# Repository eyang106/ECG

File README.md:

# ECG
Extension project for E96A: Electrocardiogram engineering design class.

Contents:
- Board and schematic files for electrocardiogram PCB

Note: To view the schematic/board, you must download the repo and open the files with EAGLE

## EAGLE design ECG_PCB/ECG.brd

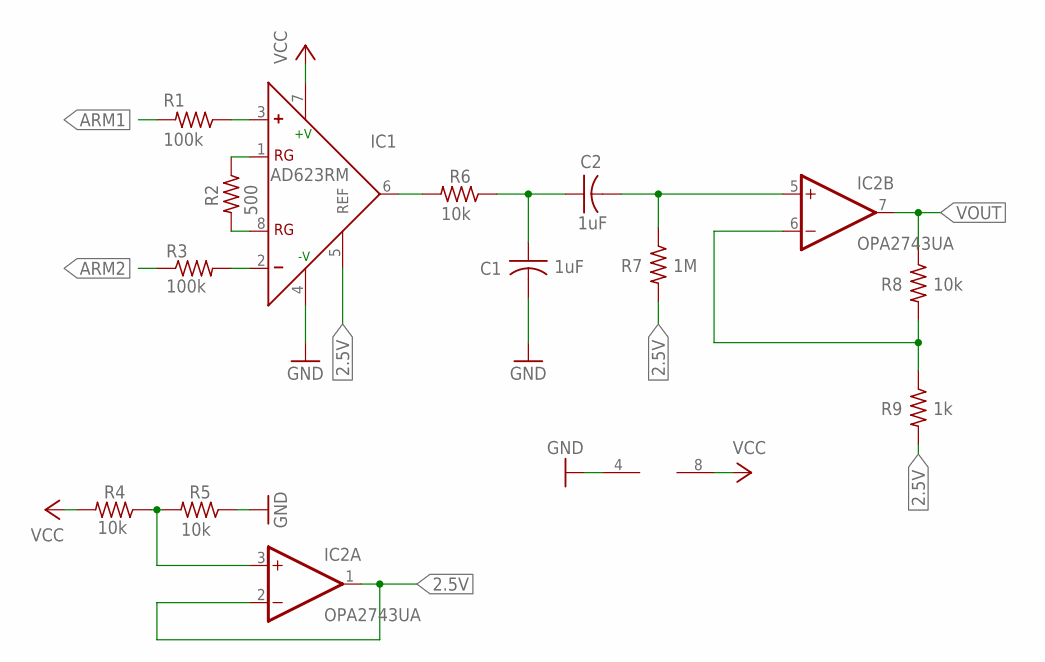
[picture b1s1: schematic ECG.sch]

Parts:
C1, C2: 1uF; C0805
IC1: AD623RM; MSOP08
IC2: OPA2743UA; SOIC8
R1, R3: 100k; R0805
R2: 500; R0805
R4, R5, R6, R8: 10k; R0805
R7: 1M; R0805
R9: 1k; R0805

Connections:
2.5V: IC1.5 (REF), IC2.1 (OUT), IC2.2 (-IN), R7.2, R9.2
ARM1: R1.2
ARM2: R3.1
GND: C1.2, IC1.4 (-V), IC2.4 (V-), R5.1
unnamed: IC1.3 (+), R1.1
unnamed: IC1.1 (RG), R2.1
unnamed: IC1.8 (RG), R2.2
unnamed: IC1.2 (-), R3.2
unnamed: IC2.3 (+IN), R4.1, R5.2
unnamed: C2.2, IC2.5 (+IN), R7.1
unnamed: IC1.6 (OUT), R6.2
unnamed: C1.1, C2.1, R6.1
unnamed: IC2.6 (-IN), R8.2, R9.1
VCC: IC1.7 (+V), IC2.8 (V+), R4.2
VOUT: IC2.7 (OUT), R8.1

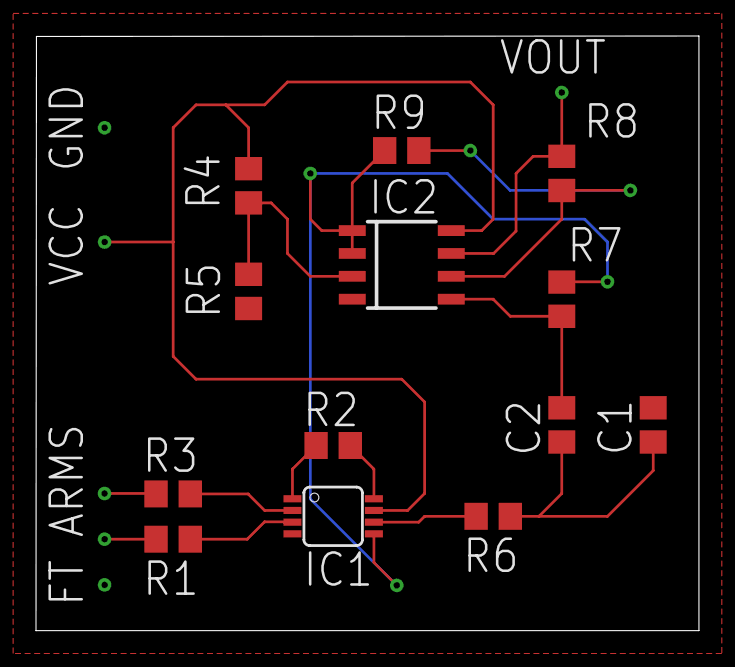
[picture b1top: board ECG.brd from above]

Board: 2 copper layers, 36.8 x 33.0 mm, 13 parts (0 on the bottom side), 13 nets.
